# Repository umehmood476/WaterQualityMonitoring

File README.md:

# WaterQualityMonitoring
IoT based Water Quality Monitoring Systems

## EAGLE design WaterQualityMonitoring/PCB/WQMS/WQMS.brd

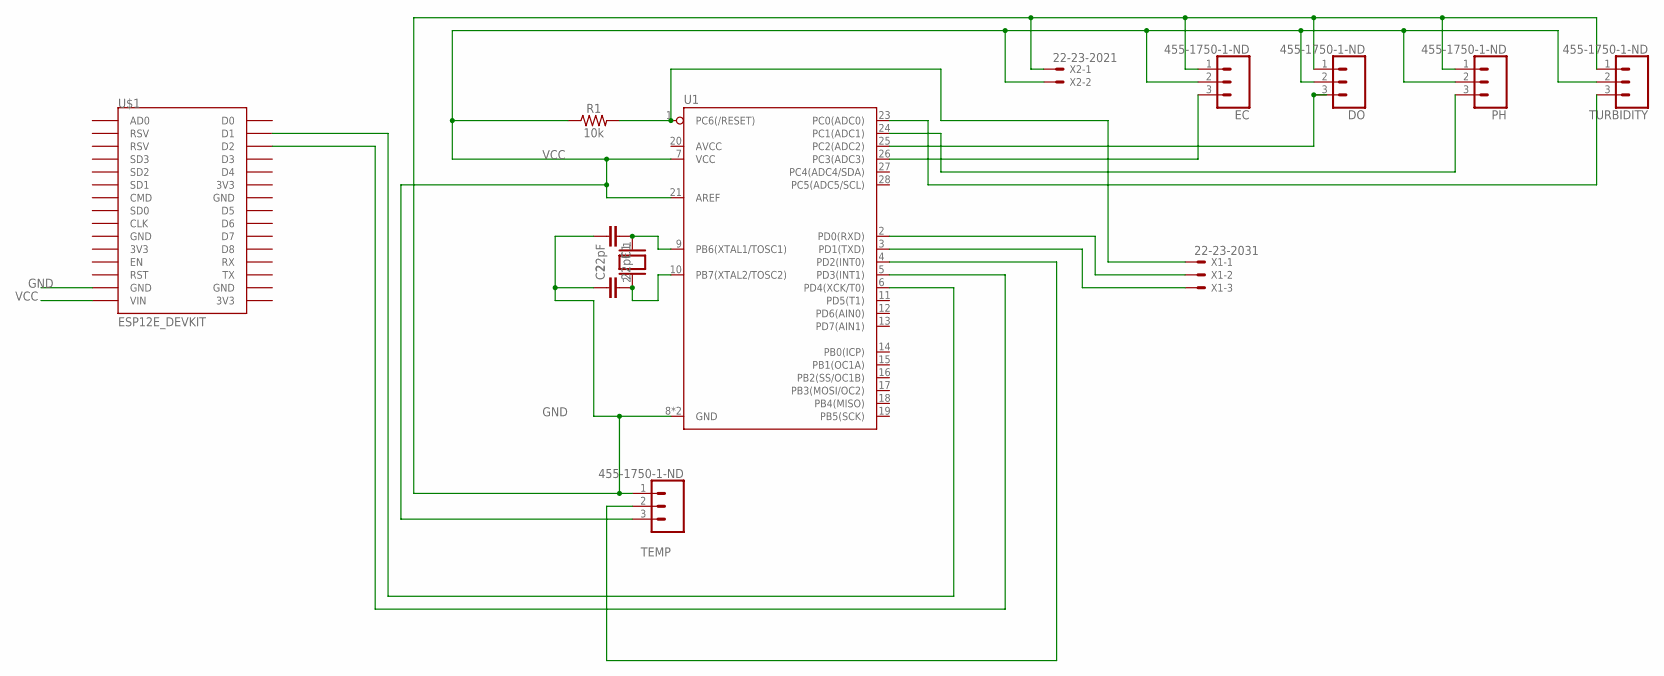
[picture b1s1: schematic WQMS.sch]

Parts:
C1, C2: 22pF; CAP-PTH-2.54
DO: 455-1750-1-ND; 1X03
EC: 455-1750-1-ND; 1X03
PH: 455-1750-1-ND; 1X03
Q1: XTAL; Q
R1: 10k; AXIAL-0.3
TEMP: 455-1750-1-ND; 1X03
TURBIDITY: 455-1750-1-ND; 1X03
U1: 328P; DIP28
U$1: ESP12E_DEVKIT
X1: 22-23-2031
X2: 22-23-2021

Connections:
GND: C1.2, C2.1, DO.1, EC.1, PH.1, TEMP.1, TURBIDITY.1, U1.8 (GND), U1.22 (GND), U$1.GND@1 (GND), X2.1
unnamed: C1.1, Q1.1, U1.9 (PB6(XTAL1/TOSC1))
unnamed: C2.2, Q1.2, U1.10 (PB7(XTAL2/TOSC2))
unnamed: TEMP.2, U1.4 (PD2(INT0))
unnamed: TURBIDITY.3, U1.23 (PC0(ADC0))
unnamed: PH.3, U1.24 (PC1(ADC1))
unnamed: DO.3, U1.25 (PC2(ADC2))
unnamed: U1.3 (PD1(TXD)), X1.3
unnamed: U1.6 (PD4(XCK/T0)), U$1.D1
unnamed: U1.5 (PD3(INT1)), U$1.D2
unnamed: EC.3, U1.26 (PC3(ADC3))
unnamed: U1.2 (PD0(RXD)), X1.2
VCC: DO.2, EC.2, PH.2, R1.P$1 (1), R1.P$2 (2), TEMP.3, TURBIDITY.2, U1.1 (PC6(/RESET)), U1.7 (VCC), U1.21 (AREF), U$1.VIN, X1.1, X2.2

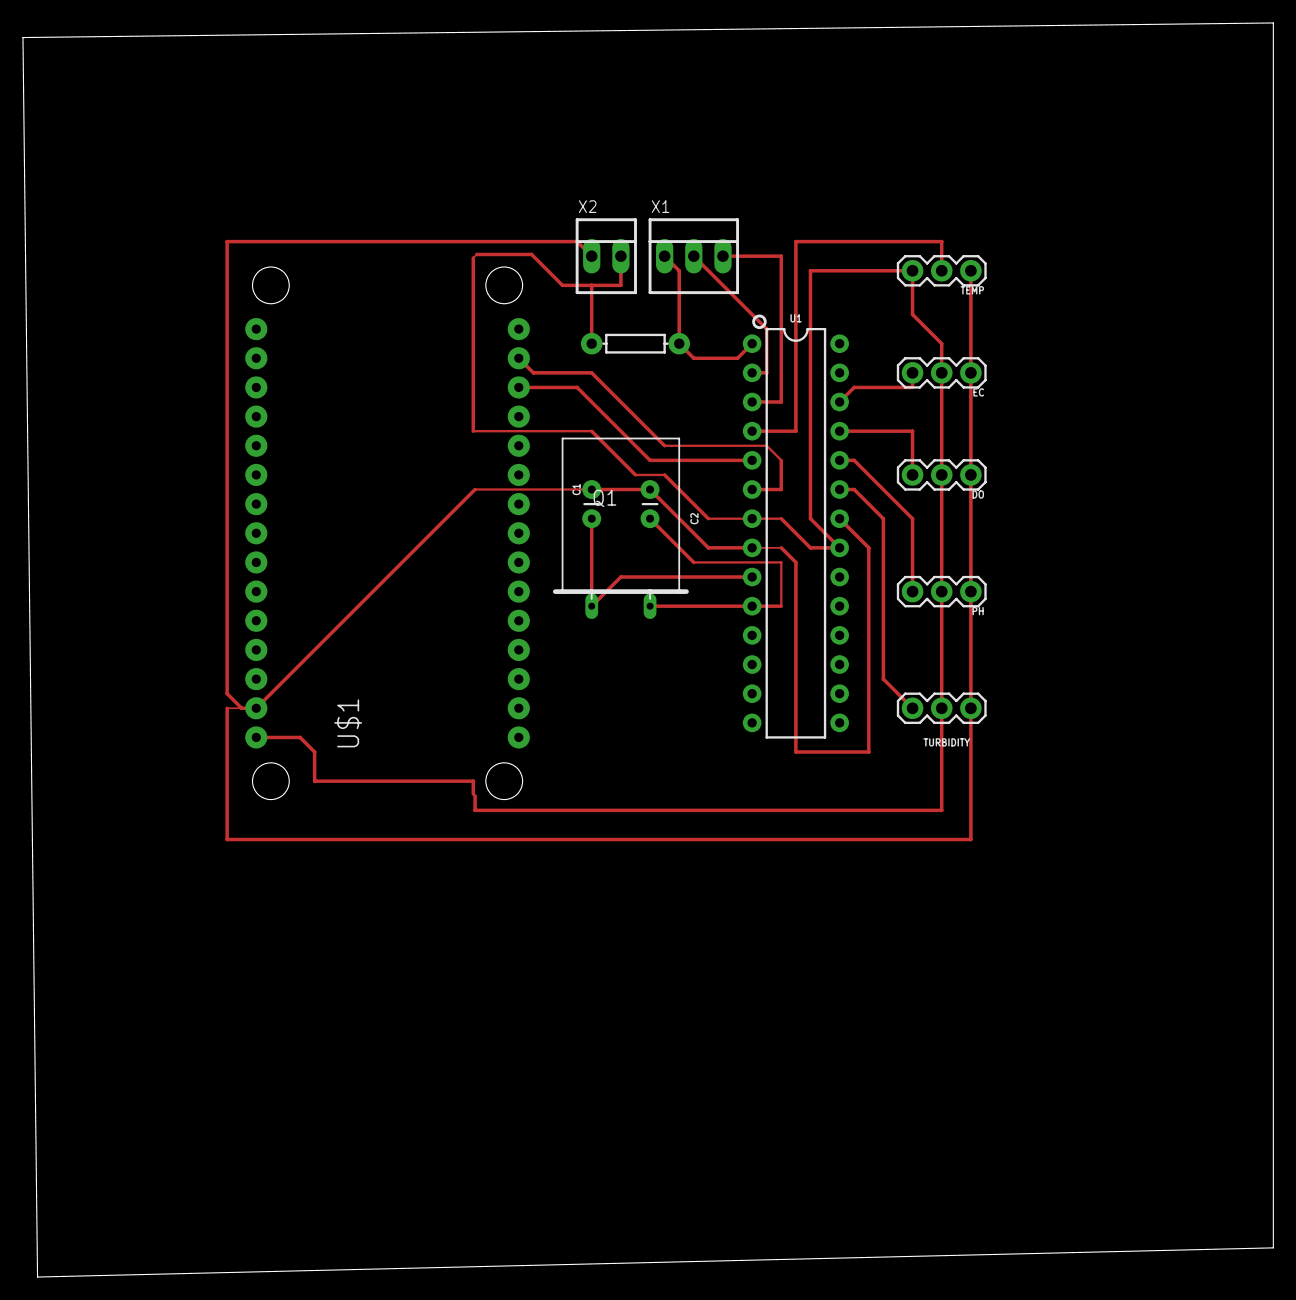
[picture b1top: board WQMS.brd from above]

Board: 2 copper layers, 108.9 x 109.2 mm, 13 parts (0 on the bottom side), 13 nets.

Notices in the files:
parts and their libraries:
SparkFun-Capacitors: Licensing: Creative Commons ShareAlike 4.0 International - https://creativecommons.org/licenses/by-sa/4.0
